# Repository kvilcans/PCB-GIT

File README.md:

Students/autors: Kristaps Vilcāns e-pasts: s5_vilcan_k@venta.lv

Studiju darbiem paredzēts GIT.

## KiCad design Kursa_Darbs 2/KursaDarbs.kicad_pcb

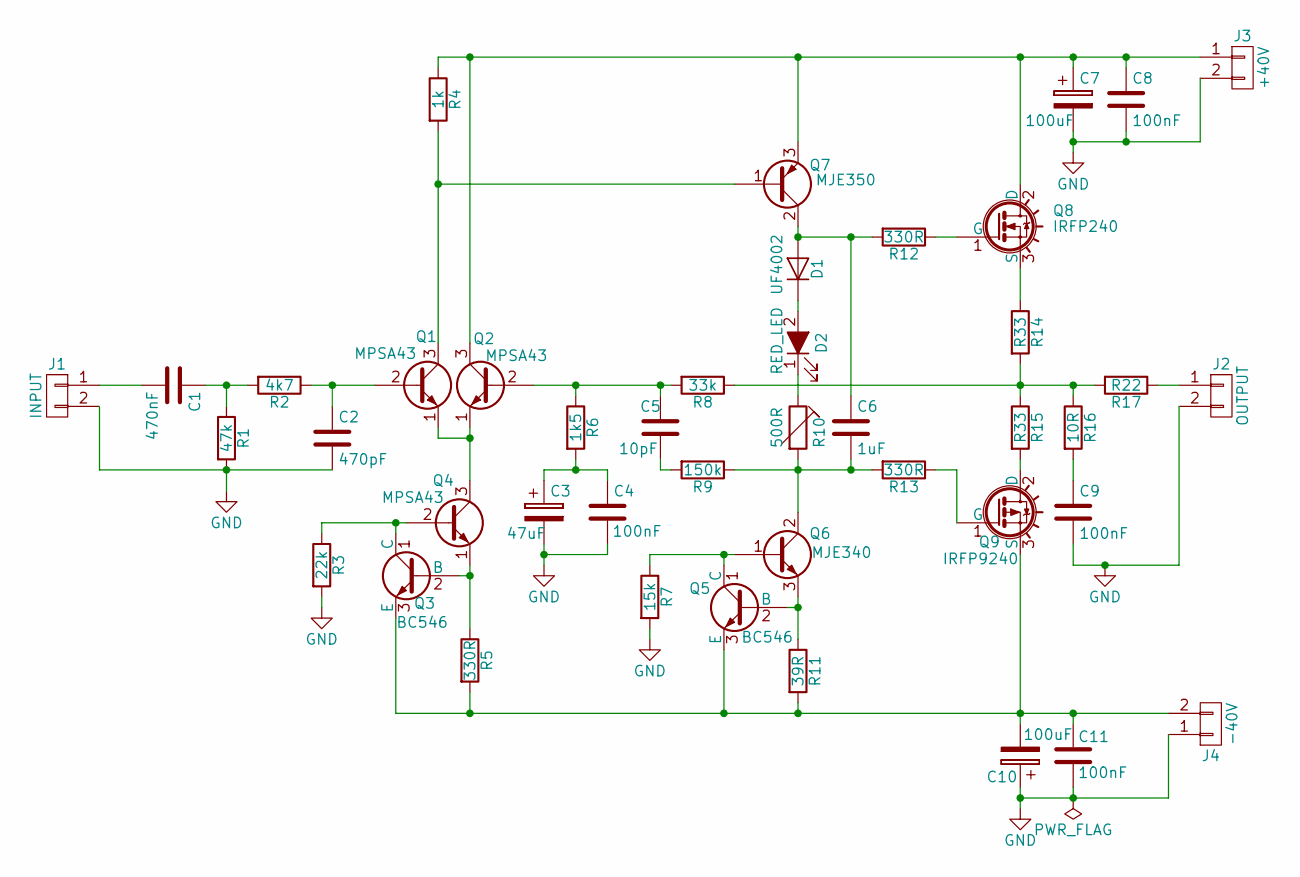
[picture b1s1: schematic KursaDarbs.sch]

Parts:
C1: 470nF; C_Rect_L7.2mm_W3.5mm_P5.00mm_FKS2_FKP2_MKS2_MKP2
C2: 470pF; C_Disc_D5.0mm_W2.5mm_P5.00mm
C3: 47uF; CP_Radial_D6.3mm_P2.50mm
C4, C8, C9, C11: 100nF; C_Rect_L7.2mm_W2.5mm_P5.00mm_FKS2_FKP2_MKS2_MKP2
C5: 10pF; C_Disc_D6.0mm_W2.5mm_P5.00mm
C6: 1uF; C_Rect_L7.2mm_W5.5mm_P5.00mm_FKS2_FKP2_MKS2_MKP2
C7, C10: 100uF; CP_Radial_D8.0mm_P3.50mm
D1: UF4002; D_DO-41_SOD81_P10.16mm_Horizontal
D2: RED_LED; LED_D5.0mm
J1: INPUT; AK300-2
J2: OUTPUT; AK300-2
J3: +40V; AK300-2
J4: -40V; AK300-2
Q1, Q2, Q4: MPSA43; TO-92_Molded_Narrow
Q3, Q5: BC546; TO-92_Molded_Narrow
Q6: MJE340; TO-126_Vertical
Q7: MJE350; TO-126_Vertical
Q8: IRFP240; TO-220_Vertical
Q9: IRFP9240; TO-220_Vertical
R1: 47k; R_Axial_DIN0207_L6.3mm_D2.5mm_P10.16mm_Horizontal
R2: 4k7; R_Axial_DIN0207_L6.3mm_D2.5mm_P10.16mm_Horizontal
R3: 22k; R_Axial_DIN0207_L6.3mm_D2.5mm_P10.16mm_Horizontal
R4: 1k; R_Axial_DIN0207_L6.3mm_D2.5mm_P10.16mm_Horizontal
R5, R12, R13: 330R; R_Axial_DIN0207_L6.3mm_D2.5mm_P10.16mm_Horizontal
R6: 1k5; R_Axial_DIN0207_L6.3mm_D2.5mm_P10.16mm_Horizontal
R7: 15k; R_Axial_DIN0207_L6.3mm_D2.5mm_P10.16mm_Horizontal
R8: 33k; R_Axial_DIN0207_L6.3mm_D2.5mm_P10.16mm_Horizontal
R9: 150k; R_Axial_DIN0207_L6.3mm_D2.5mm_P10.16mm_Horizontal
R10: 500R; Potentiometer_Trimmer_Vishay_T73XW_Vertical
R11: 39R; R_Axial_DIN0207_L6.3mm_D2.5mm_P10.16mm_Horizontal
R14, R15: R33; R_Axial_DIN0617_L17.0mm_D6.0mm_P20.32mm_Horizontal
R16: 10R; R_Axial_DIN0617_L17.0mm_D6.0mm_P20.32mm_Horizontal
R17: R22; R_Axial_DIN0918_L18.0mm_D9.0mm_P22.86mm_Horizontal

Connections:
GND: C2.2, C3.2, C4.2, C7.2, C8.2, C9.2, C10.1, C11.2, J1.2, J2.2, J3.2, J4.1, R1.2, R3.2, R7.2
unnamed: C1.1, R1.1, R2.2
unnamed: C1.2, J1.1
unnamed: C2.1, Q1.2 (B), R2.1
unnamed: C3.1, C4.1, R6.2
unnamed: C5.1, Q2.2 (B), R6.1, R8.2
unnamed: C5.2, R9.2
unnamed: C6.1, D1.2 (A), Q7.2 (C), R12.2
unnamed: C6.2, Q6.2 (C), R9.1, R10.2, R13.2
unnamed: C7.1, C8.1, J3.1, Q2.3 (C), Q7.3 (E), Q8.2 (D), R4.1
unnamed: C9.1, R16.2
unnamed: C10.2, C11.1, J4.2, Q3.3 (E), Q5.3 (E), Q9.3 (S), R5.2, R11.2
unnamed: D1.1 (K), D2.2 (A)
unnamed: D2.1 (K), R10.1
unnamed: J2.1, R17.1
unnamed: Q1.1 (E), Q2.1 (E), Q4.3 (C)
unnamed: Q1.3 (C), Q7.1 (B), R4.2
unnamed: Q3.1 (C), Q4.2 (B), R3.1
unnamed: Q3.2 (B), Q4.1 (E), R5.1
unnamed: Q5.1 (C), Q6.1 (B), R7.1
unnamed: Q5.2 (B), Q6.3 (E), R11.1
unnamed: Q8.1 (G), R12.1
unnamed: Q8.3 (S), R14.1
unnamed: Q9.1 (G), R13.1
unnamed: Q9.2 (D), R15.2
unnamed: R8.1, R14.2, R15.1, R16.1, R17.2

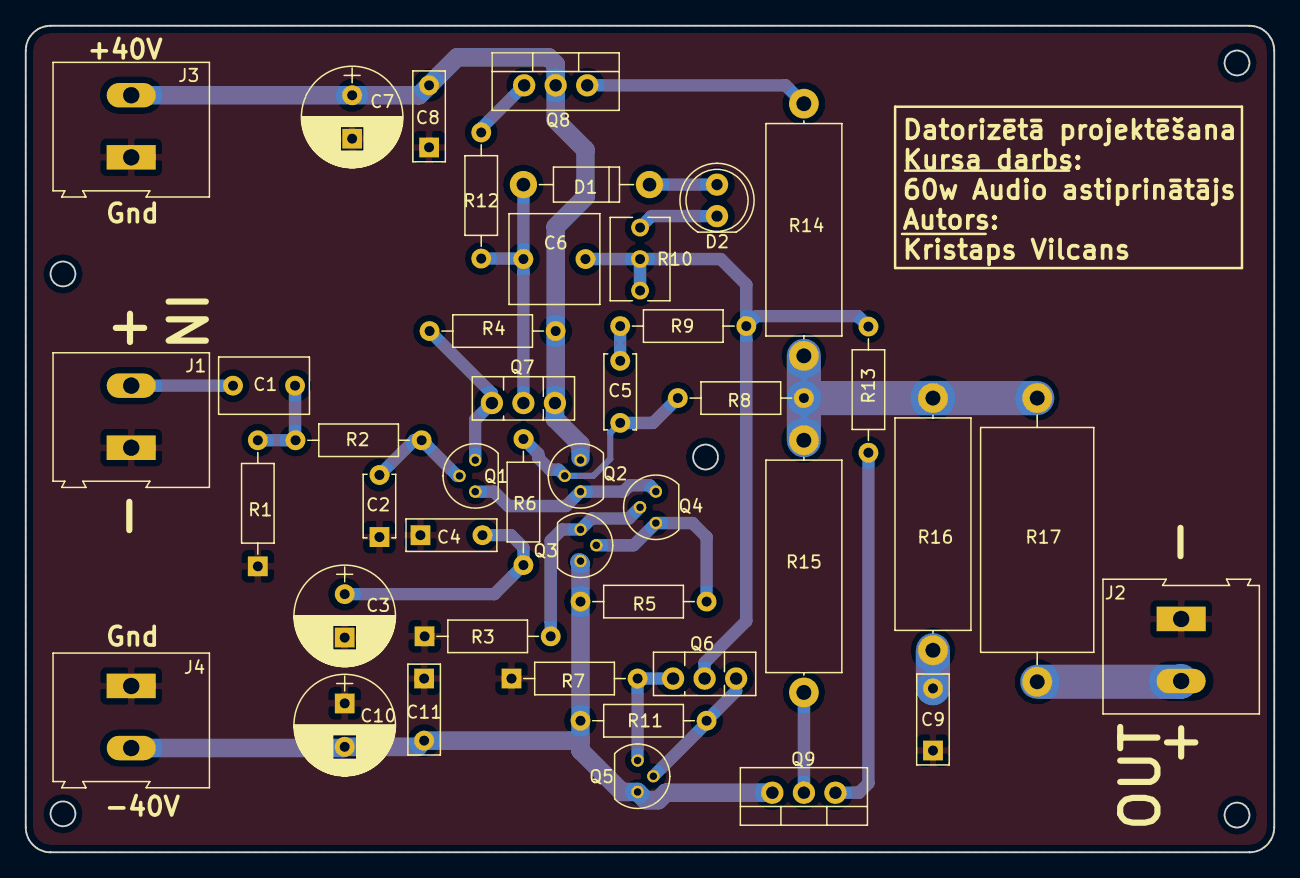
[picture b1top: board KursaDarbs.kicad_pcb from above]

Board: 2 copper layers, 100.6 x 66.6 mm, 43 parts (0 on the bottom side), 26 nets.

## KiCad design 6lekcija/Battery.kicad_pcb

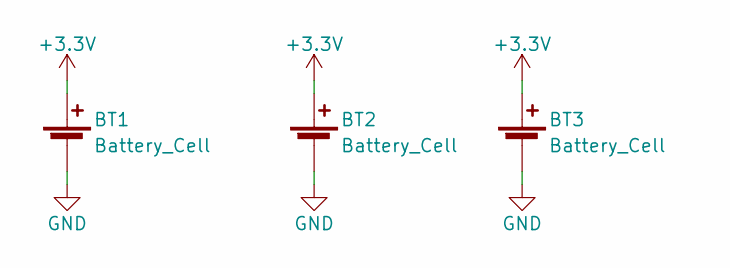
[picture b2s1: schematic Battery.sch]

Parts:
BT1: Battery_Cell; SMTU2032
BT2: Battery_Cell; S8211R
BT3: Battery_Cell; SMTU1225-LF

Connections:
+3V3: BT1.1 (+), BT2.1 (+), BT3.1 (+)
GND: BT1.2 (-), BT2.2 (-), BT3.2 (-)

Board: 2 copper layers, 3 parts (0 on the bottom side), 2 nets, no tracks yet.

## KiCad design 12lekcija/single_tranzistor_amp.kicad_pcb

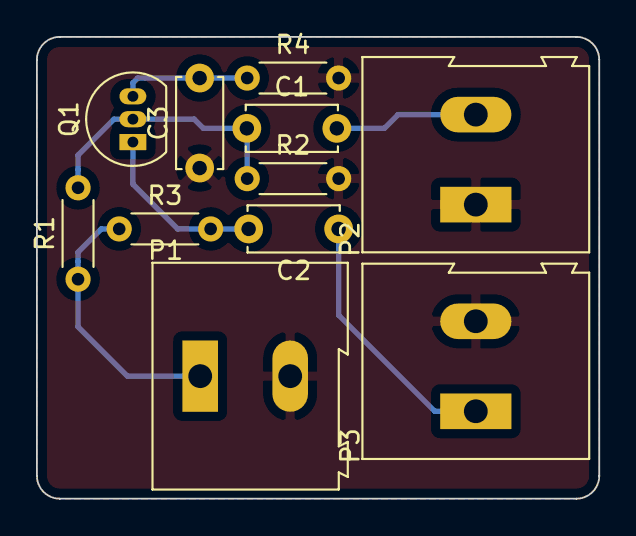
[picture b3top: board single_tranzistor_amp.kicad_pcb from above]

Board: 2 copper layers, 31.2 x 25.7 mm, 11 parts (0 on the bottom side), 7 nets.

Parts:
C1, C2: 20uF; C_Disc_D5.0mm_W2.5mm_P5.00mm
C3: 50uF; C_Disc_D5.0mm_W2.5mm_P5.00mm
P1: PWR_CONN; AK300-2
P2: SIGNAL_IN; AK300-2
P3: SIGNAL_OUT; AK300-2
Q1: BC548; TO-92_Inline_Narrow_Oval
R1: 22k; R_Axial_DIN0204_L3.6mm_D1.6mm_P5.08mm_Horizontal
R2: 6.8k; R_Axial_DIN0204_L3.6mm_D1.6mm_P5.08mm_Horizontal
R3: 4.7k; R_Axial_DIN0204_L3.6mm_D1.6mm_P5.08mm_Horizontal
R4: 1.8k; R_Axial_DIN0204_L3.6mm_D1.6mm_P5.08mm_Horizontal

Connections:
+12V: P1.1, R1.1, R3.1
GND: C3.1, P1.2, P2.1, P3.2, R2.2, R4.2
unnamed: C1.1, Q1.2, R1.2, R2.1
unnamed: C1.2, P2.2
unnamed: C2.1, P3.1
unnamed: C2.2, Q1.1, R3.2
unnamed: C3.2, Q1.3, R4.1

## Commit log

2017-05-18 Jauna Git izveide
2017-05-18 Readme update
2017-05-18 Jaunajā repozitorijā pievieno vecos(nepazaudētos)/jaunos failus
2017-05-18 Mazliet sakārtoju darbus
2017-05-25 iepriekšējo lekciju papildinājums un kursa darba sākums
2017-05-25 lekciju papildinajums
2017-05-25 iepriekseju lekciju papildinajums
2017-06-15 3Lekcijas darba papildinajums
    3Lekcijas darba papildinajums
2017-06-15 6Lekcijas darba pabeigshana
2017-06-15 7Lekcijas papildinajums
2017-06-15 Kursa darba papildinajums, lekciju darbu nobeigums
2017-06-16 PCB Edit #1
2017-06-16 Kursa darba edits #2
2017-06-17 Kursa Darbs done
2017-06-17 Gerber edits heh
2017-06-17 Monteshanas urbumu korekcija
2017-06-17 trimmer potentiometra labojums
2017-06-17 12lekcijas papildinajums
